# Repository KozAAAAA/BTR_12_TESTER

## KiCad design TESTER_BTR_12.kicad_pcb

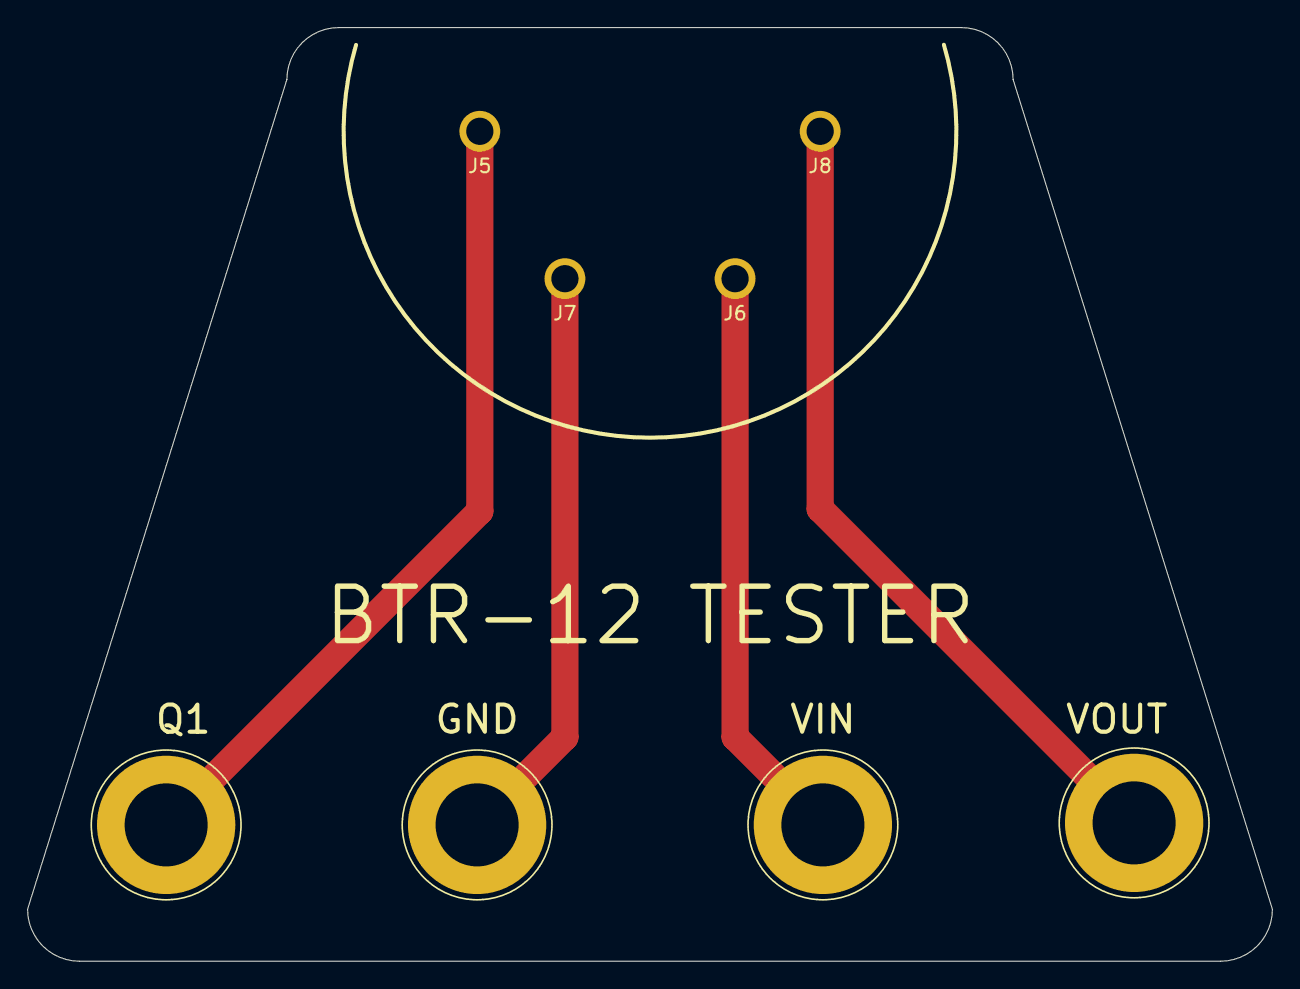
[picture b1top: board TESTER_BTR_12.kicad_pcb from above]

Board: 2 copper layers, 91.4 x 68.6 mm, 8 parts (0 on the bottom side), 4 nets.

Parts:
GND: Conn_01x01_Female; Banana_Jack_1Pin
J5, J6, J7, J8: Conn_01x01_Female; conn_BTR_12
Q1: Conn_01x01_Female; Banana_Jack_1Pin
VIN: Conn_01x01_Female; Banana_Jack_1Pin
VOUT: Conn_01x01_Female; Banana_Jack_1Pin

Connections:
unnamed: GND.1, J7.1
unnamed: J5.1, Q1.1
unnamed: J6.1, VIN.1
unnamed: J8.1, VOUT.1

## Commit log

2022-02-08 First version of btr_12 tester
2022-02-08 Added the .txt file and edited the line names
2022-02-11 New connectors, board has to be changed to 5 pins
2022-02-16 Updated the .txt
